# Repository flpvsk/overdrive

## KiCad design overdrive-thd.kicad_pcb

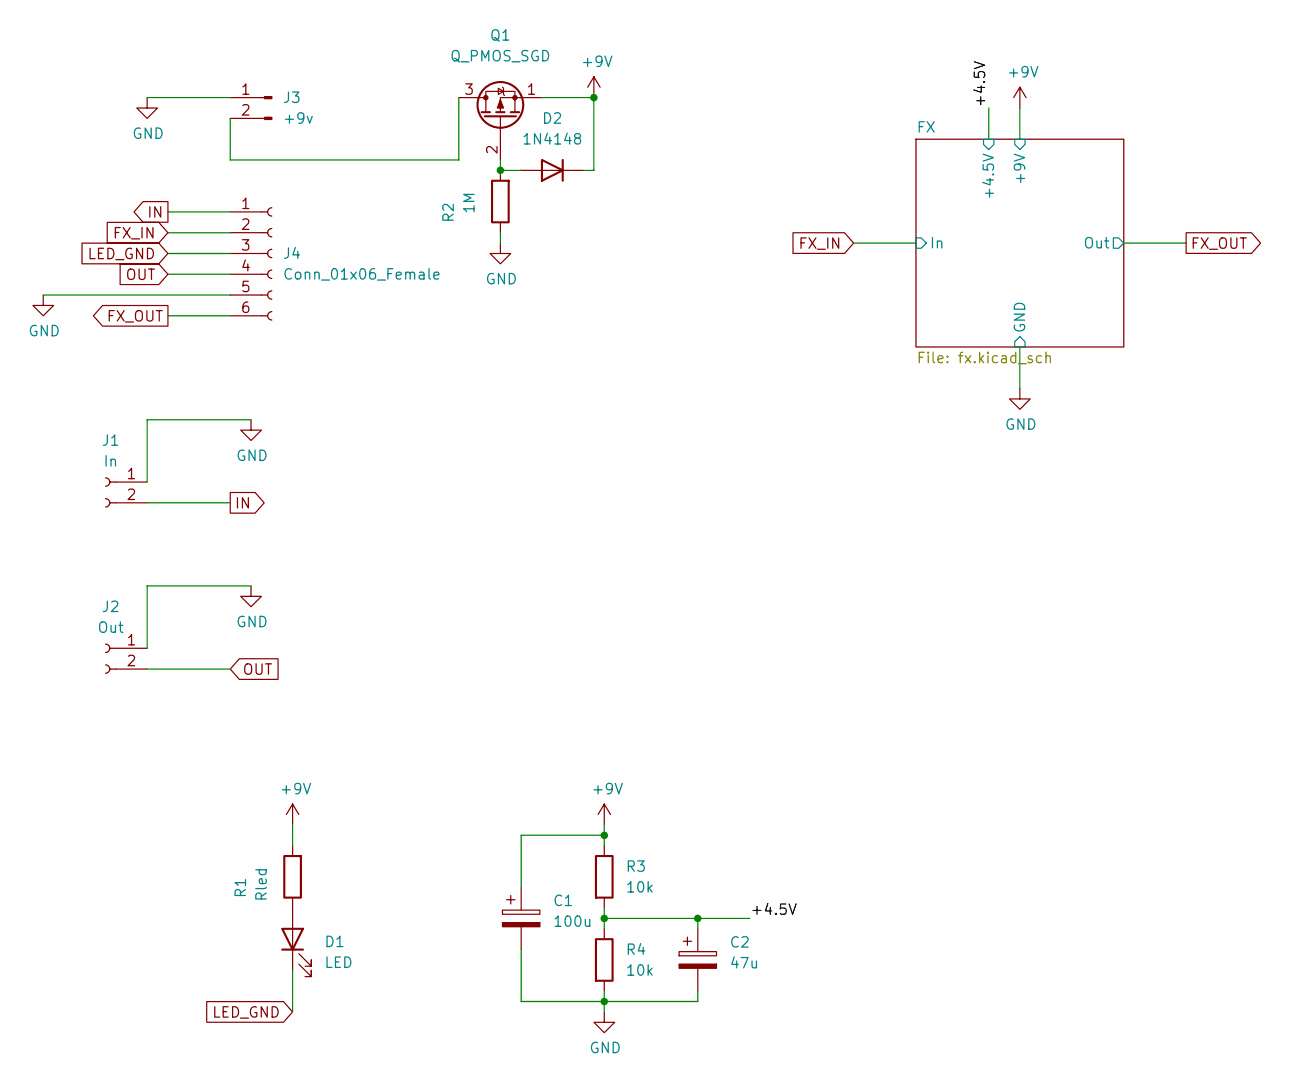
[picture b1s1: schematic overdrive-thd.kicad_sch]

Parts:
C1: 100u; CP_Radial_D5.0mm_P2.50mm
C2: 47u; CP_Radial_D5.0mm_P2.50mm
D1: LED; LED_D5.0mm
D2: 1N4148; D_A-405_P7.62mm_Horizontal
J1: In; PinHeader_1x02_P2.54mm_Vertical
J2: Out; PinHeader_1x02_P2.54mm_Vertical
J3: +9v; JST_XH_B2B-XH-A_1x02_P2.50mm_Vertical
J4: Conn_01x06_Female; PinHeader_1x06_P2.54mm_Vertical
Q1: Q_PMOS_SGD; TO-92L_Inline_Wide
R1: Rled; R_Axial_DIN0207_L6.3mm_D2.5mm_P7.62mm_Horizontal
R2: 1M; R_Axial_DIN0207_L6.3mm_D2.5mm_P7.62mm_Horizontal
R3, R4: 10k; R_Axial_DIN0207_L6.3mm_D2.5mm_P7.62mm_Horizontal

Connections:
+9V: C1.1, D2.1 (K), Q1.1 (S), R1.2, R3.1; also elsewhere on the board
/+4.5V: C2.1, R3.2, R4.1; also elsewhere on the board
FX_IN: J4.2; also elsewhere on the board
FX_OUT: J4.6; also elsewhere on the board
GND: C1.2, C2.2, J1.1, J2.1, J3.1, J4.5, R2.1, R4.2; also elsewhere on the board
IN: J1.2, J4.1
LED_GND: D1.1 (K), J4.3
unnamed: D1.2 (A), R1.1
unnamed: D2.2 (A), Q1.2 (G), R2.2
unnamed: J3.2, Q1.3 (D)
OUT: J2.2, J4.4

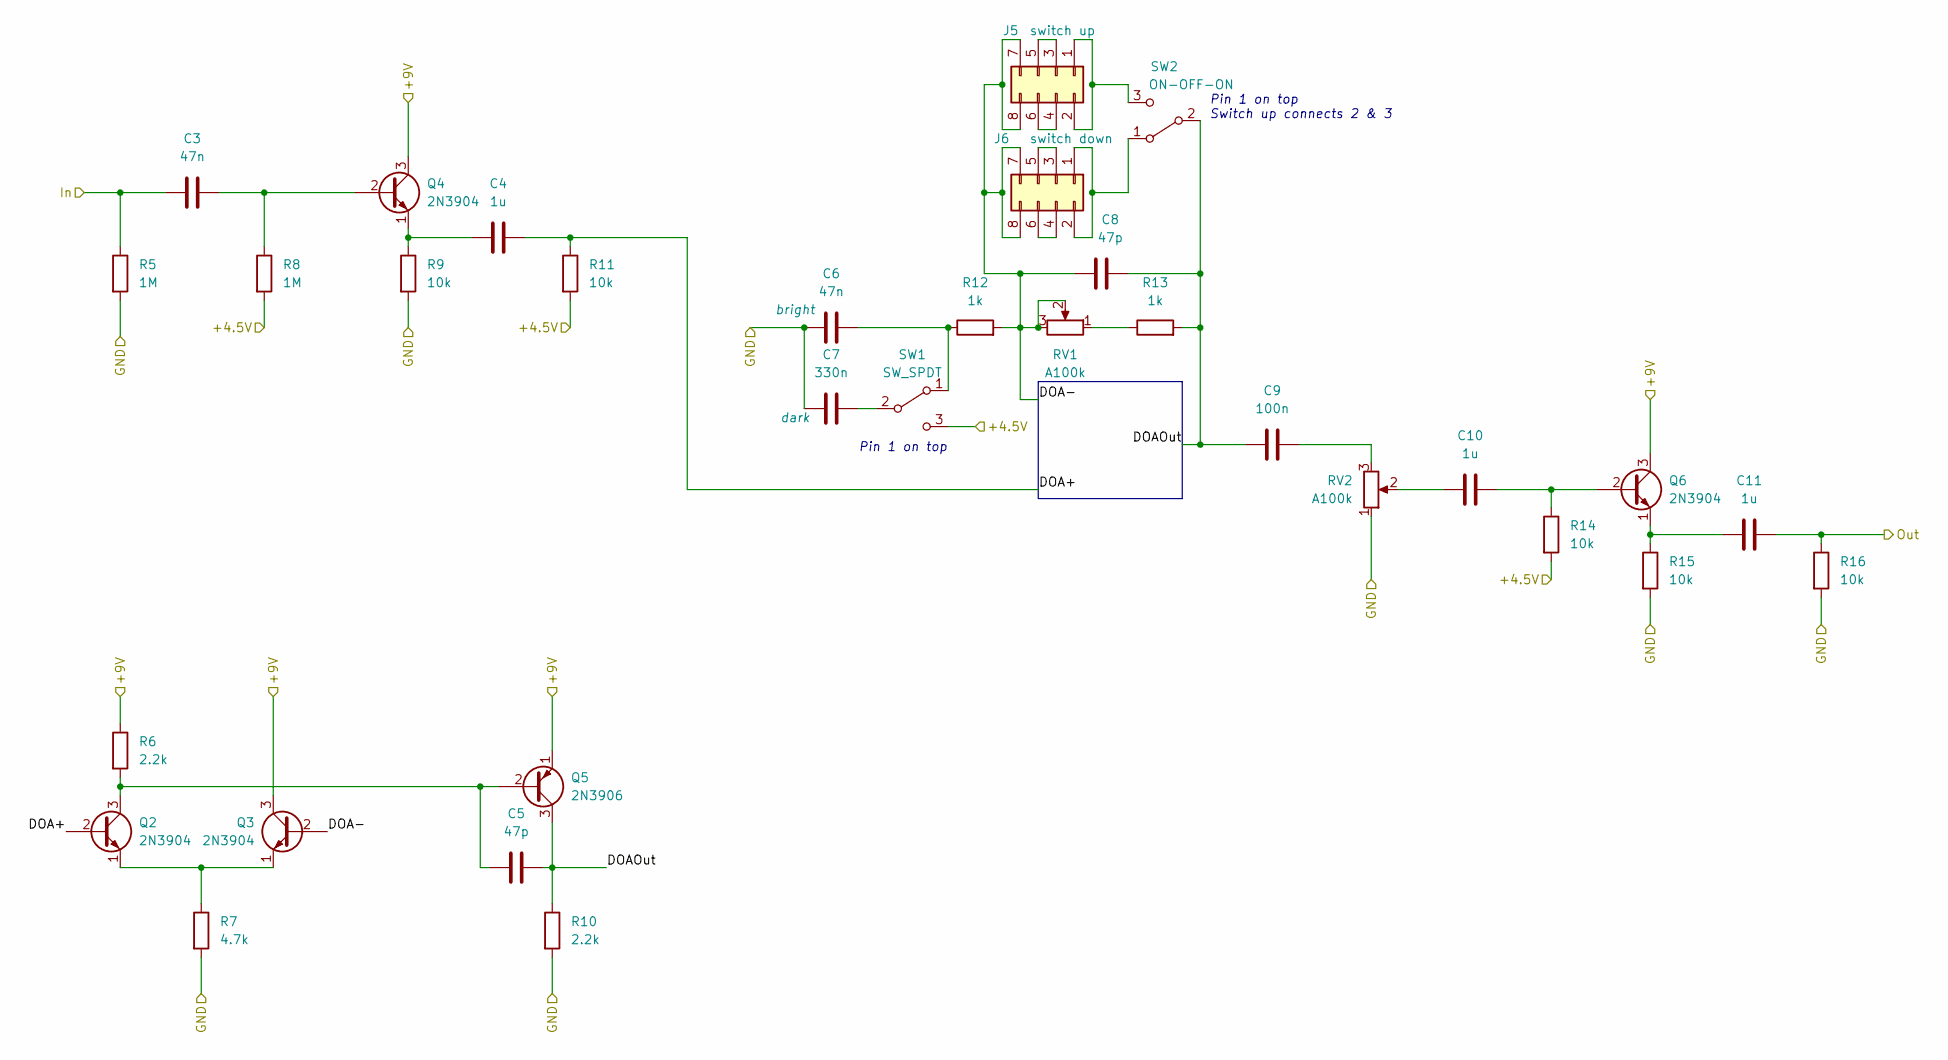
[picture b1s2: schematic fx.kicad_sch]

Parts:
C3, C6: 47n; C_Rect_L7.0mm_W2.5mm_P5.00mm
C4, C10, C11: 1u; C_Rect_L7.0mm_W4.5mm_P5.00mm
C5, C8: 47p; C_Disc_D7.0mm_W2.5mm_P5.00mm
C7: 330n; C_Rect_L7.0mm_W2.5mm_P5.00mm
C9: 100n; C_Rect_L7.0mm_W2.5mm_P5.00mm
J5: switch up; PinHeader_2x04_P2.54mm_Vertical
J6: switch down; PinHeader_2x04_P2.54mm_Vertical
Q2, Q3, Q4, Q6: 2N3904; TO-92L_Inline_Wide
Q5: 2N3906; TO-92L_Inline_Wide
R5, R8: 1M; R_Axial_DIN0207_L6.3mm_D2.5mm_P7.62mm_Horizontal
R6, R10: 2.2k; R_Axial_DIN0207_L6.3mm_D2.5mm_P7.62mm_Horizontal
R7: 4.7k; R_Axial_DIN0207_L6.3mm_D2.5mm_P7.62mm_Horizontal
R9, R11, R14, R15, R16: 10k; R_Axial_DIN0207_L6.3mm_D2.5mm_P7.62mm_Horizontal
R12, R13: 1k; R_Axial_DIN0207_L6.3mm_D2.5mm_P7.62mm_Horizontal
RV1, RV2: A100k; 16MM_B.MOUNT_BANZAI
SW1: SW_SPDT; SPDT.LUGS.PM
SW2: ON-OFF-ON; SPDT.LUGS.PM

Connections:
+9V: Q3.3 (C), Q4.3 (C), Q5.1 (E), Q6.3 (C), R6.1; also elsewhere on the board
/+4.5V: R8.2, R11.2, R14.2, SW1.3 (C); also elsewhere on the board
/FX/DOA+: C4.2, Q2.2 (B), R11.1
/FX/DOA-: C8.1, J5.7, J5.8, J6.7, J6.8, Q3.2 (B), R12.2, RV1.2, RV1.3
/FX/DOAOut: C5.2, C8.2, C9.1, Q5.3 (C), R10.1, R13.2, SW2.2 (B)
FX_IN: C3.1, R5.1; also elsewhere on the board
FX_OUT: C11.2, R16.1; also elsewhere on the board
GND: C6.1, C7.1, R5.2, R7.2, R9.2, R10.2, R15.2, R16.2, RV2.1; also elsewhere on the board
unnamed: C3.2, Q4.2 (B), R8.1
unnamed: C4.1, Q4.1 (E), R9.1
unnamed: C5.1, Q2.3 (C), Q5.2 (B), R6.2
unnamed: C6.2, R12.1, SW1.1 (A)
unnamed: C7.2, SW1.2 (B)
unnamed: C9.2, RV2.3
unnamed: C10.1, RV2.2
unnamed: C10.2, Q6.2 (B), R14.1
unnamed: C11.1, Q6.1 (E), R15.1
unnamed: J5.1, J5.2, SW2.3 (C)
unnamed: J5.3, J5.5
unnamed: J5.4, J5.6
unnamed: J6.1, J6.2, SW2.1 (A)
unnamed: J6.3, J6.5
unnamed: J6.4, J6.6
unnamed: Q2.1 (E), Q3.1 (E), R7.1
unnamed: R13.1, RV1.1

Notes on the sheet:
Pin 1 on top Switch up connects 2 & 3
Pin 1 on top

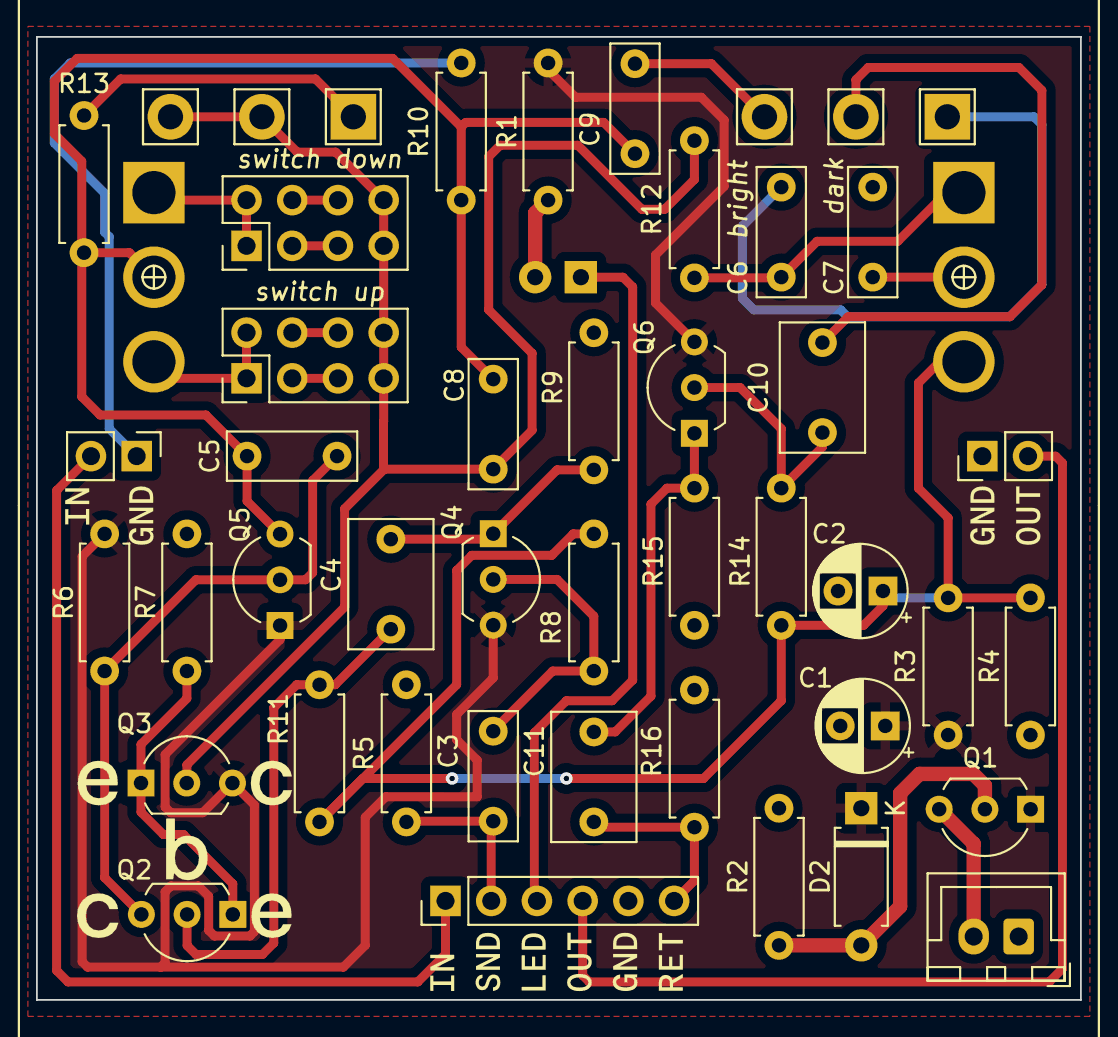
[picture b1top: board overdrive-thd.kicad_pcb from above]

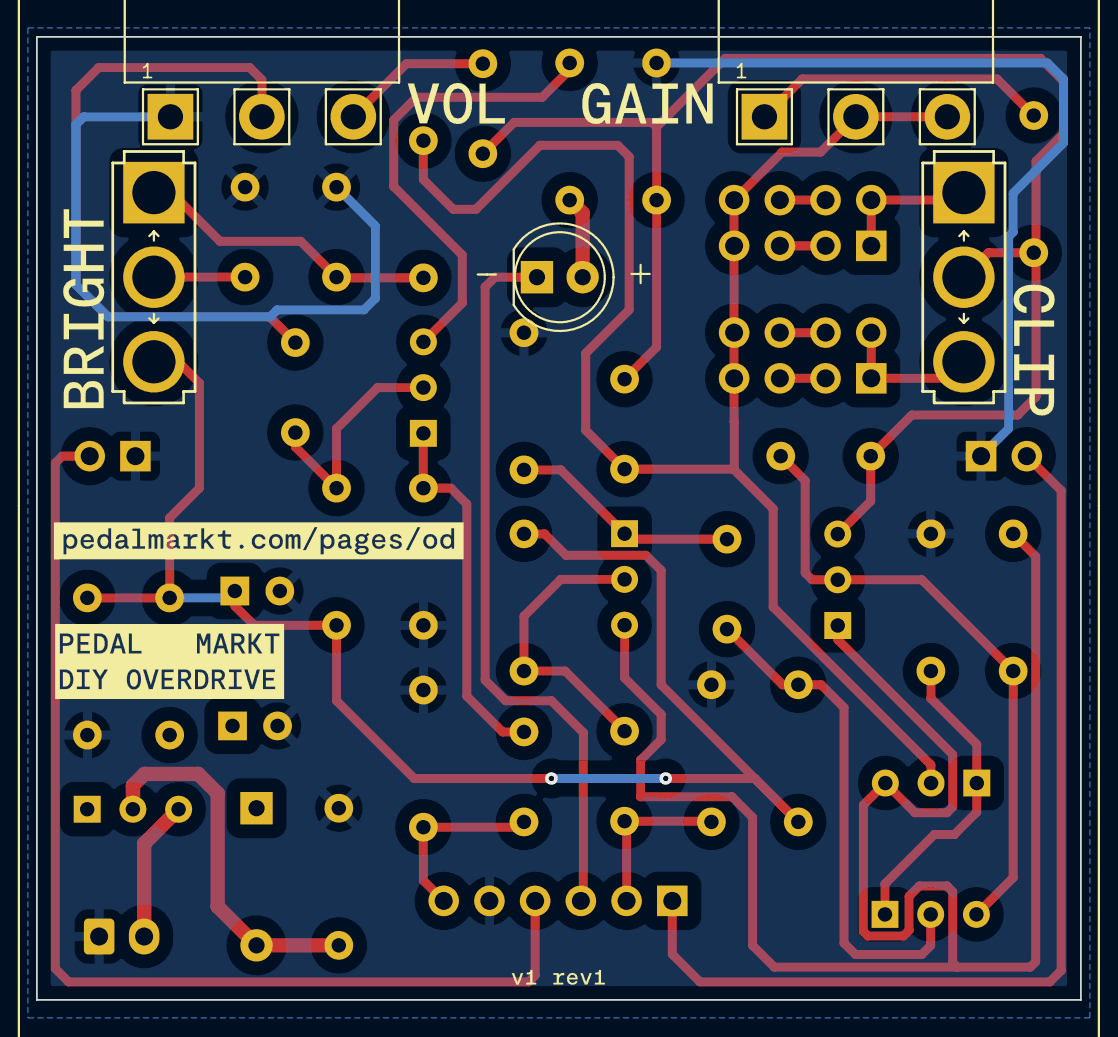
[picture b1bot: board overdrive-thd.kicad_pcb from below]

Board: 2 copper layers, 58.0 x 53.5 mm, 67 parts (10 on the bottom side), 31 nets.

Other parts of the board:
kibuzzard-669A4B96: G***; kibuzzard-669A4B96
kibuzzard-669A4BB1: G***; kibuzzard-669A4BB1
kibuzzard-669A47AF: G***; kibuzzard-669A47AF
kibuzzard-669A47EC: G***; kibuzzard-669A47EC
kibuzzard-669A474F: G***; kibuzzard-669A474F
kibuzzard-669A481A: G***; kibuzzard-669A481A
kibuzzard-669A4792: G***; kibuzzard-669A4792
kibuzzard-6618FB6D: G***; kibuzzard-6618FB6D
kibuzzard-6618FB68, kibuzzard-6618FB68#2: G***; kibuzzard-6618FB68
kibuzzard-6618FB72, kibuzzard-6618FB72#2: G***; kibuzzard-6618FB72
kibuzzard-6618FE8B, kibuzzard-6618FE8B#2: G***; kibuzzard-6618FE8B
kibuzzard-6618FE9C: G***; kibuzzard-6618FE9C
kibuzzard-6618FE93: G***; kibuzzard-6618FE93
kibuzzard-6618FEA0, kibuzzard-6618FEA0#2: G***; kibuzzard-6618FEA0
kibuzzard-6618FEAA, kibuzzard-6618FEAA#2, kibuzzard-6618FEAA#3: G***; kibuzzard-6618FEAA
kibuzzard-6618FEB1: G***; kibuzzard-6618FEB1

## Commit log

2024-07-18 OD schem
2024-07-18 init layout
2024-07-19 Routing complete
